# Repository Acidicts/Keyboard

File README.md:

# Keyboard

Sooo, this is a keyboard with a fun little oled display (via i2c) and rotary encoder with some rgb leds, following a modified ansi layout: `"` and `@` are swapped

### Features
- Powered via usb-c
- Wired keyboard
- RP2354A (2MB on onboard memory)
- RGB LEDS

### Models
- [Keyboard Assembly  (web)](https://a360.co/476DL3y)
- [Keyboard Assembly  (f3z)](Assembly.f3z)
- [Keyboard Case      (step)](./case/Case.step)
- [Keyboard Top Plate (step)](./case/Top-Plate.step)

### Assembly
- The case is a bit bigger than most 3d printers so you may need a 3rd party service for it
- Any ansi keycap set compatible with 75% keyboards should work i have not included price for them as you can make them in many ways,  either buy, 3d print, etc
- feel free to swap the `@` and `"` back if you prefer it that way just edit the [main.py](/firmware/main.py)
1. I recommend using PCBA for the top layer as those parts may be difficult to solder
2. On arrival of your half made pcb, start with soldering on the diodes facing in the direction of the silkscreen diagram
3. After solder on the rgb leds matching the notch up to the silkscreen too
4. Finally solder on your key switches to the board (I didn't want to give anyone the pain of manually soldering hot swaps on)
5. Put on your keycaps to key switches
6. Use a soldering iron to put in a m3 heat insert into the hole in the case
7. Put the pcb in the case
8. use a m3 screw to firmly mount to case but be wary of the underneath components so use spacers for it

### Case
[case](/case/Case.step)
[https://a360.co/476DL3y](https://a360.co/476DL3y)

### Firmware
1. Download the latest release of circuitpython from [here](https://downloads.circuitpython.org/bin/seeeduino_xiao_rp2040/en_GB/adafruit-circuitpython-seeeduino_xiao_rp2040-en_GB-10.3.0.uf2)
2. whilst powering the board (by plugging in usbc) hold down the boot button(labelled as `SW1` and plug it into your computer. The board should show up as a USB drive called `RPI-RP2` or something similar.
3. Drag and drop the downloaded UF2 file onto the `RPI-RP2` drive. The board will reboot and show up as a USB drive called `CIRCUITPY`.
4. drag and drop the contents of the [`firmware`](./firmware) folder onto the `CIRCUITPY` drive.
5. Restart the board and it should now be ready to use.

### BOMs
| Name | Link |
| --- | --- |
| Overview | [here](./BOM.csv) |
| LCSC List (included in addition parts) | [here](./BOMS/LCSC_BOM.csv) |
| PCBA Parts | [here](./BOMS/jlcpcb_pcb_BOM.csv) |

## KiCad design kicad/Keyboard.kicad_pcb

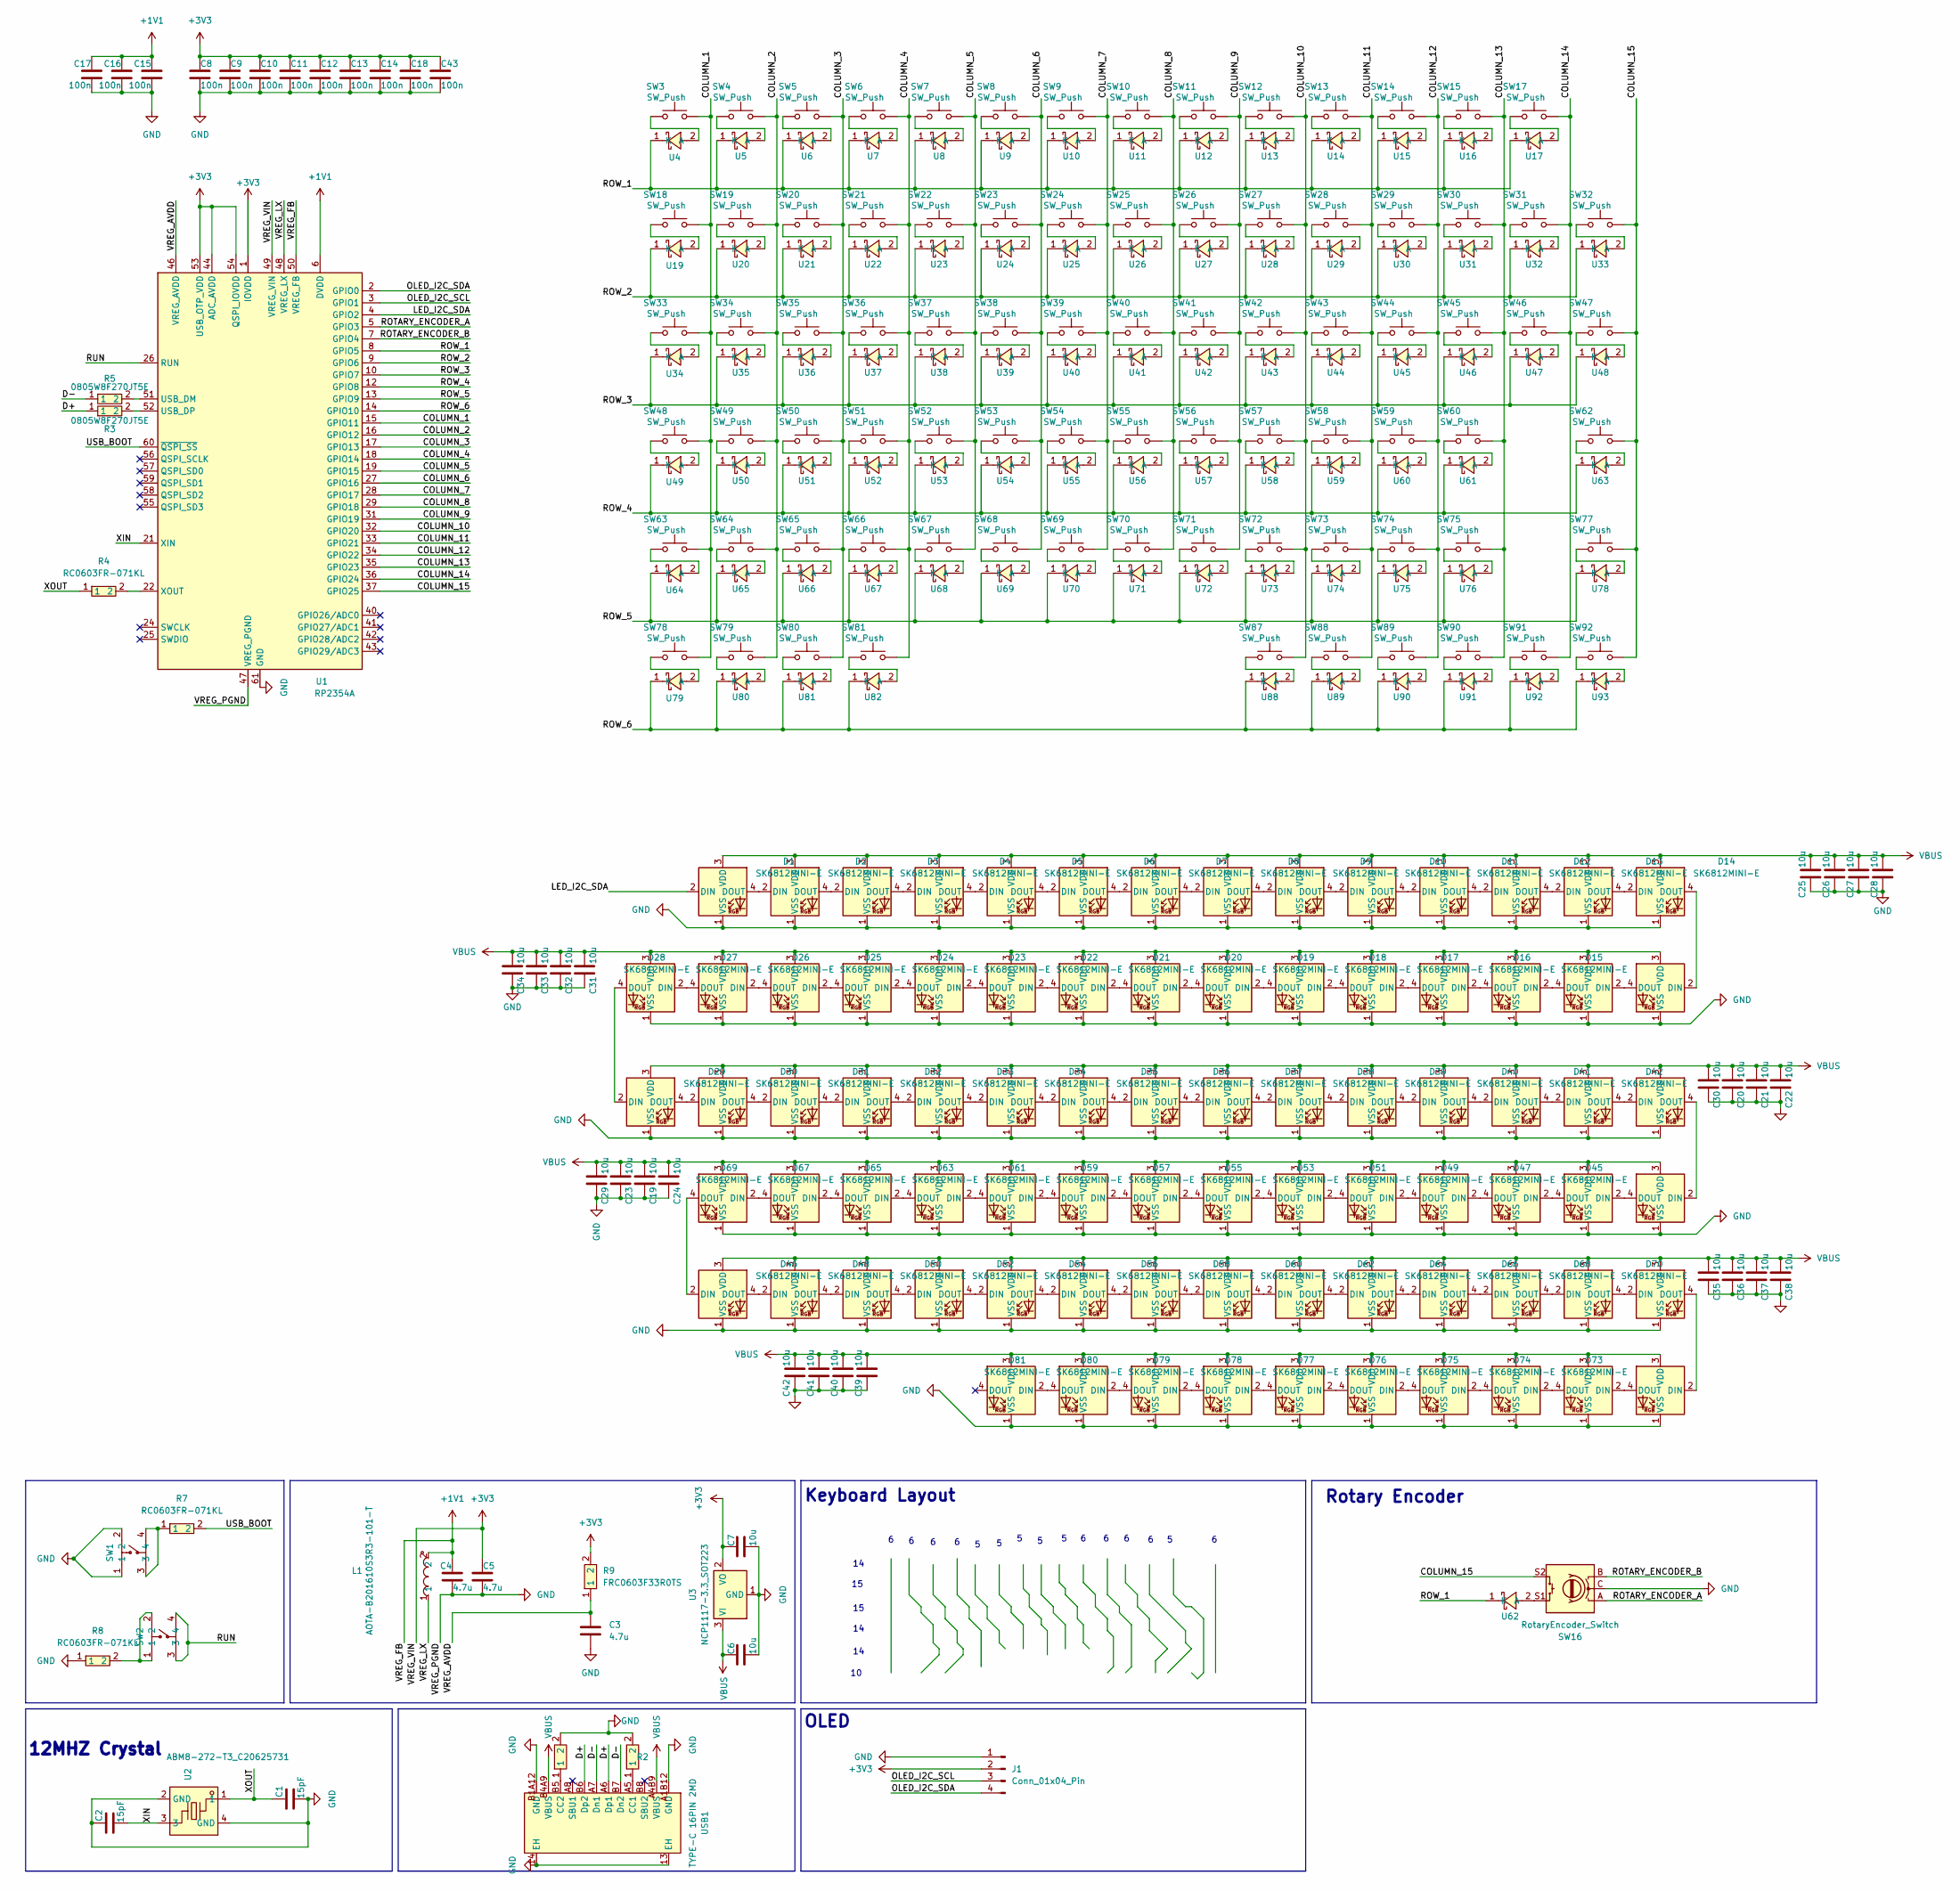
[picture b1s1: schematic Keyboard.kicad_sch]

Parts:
C1, C2: 15pF; C_0603_1608Metric
C3, C4, C5: 4.7u; C_0603_1608Metric
C6, C7, C19, C20, C21, C22, C23, C24, C25, C26, C27, C28, C29, C30, C31, C32, C33, C34, C35, C36, C37, C38, C39, C40, C41, C42: 10u; C_0805_2012Metric
C8, C9, C10, C11, C12, C13, C14, C15, C16, C17, C18, C43: 100n; C_0603_1608Metric
D1, D2, D3, D4, D5, D6, D7, D8, D9, D10, D11, D12, D13, D14, D15, D16, D17, D18, D19, D20, D21, D22, D23, D24, D25, D26, D27, D28, D29, D30, D31, D32, D33, D34, D35, D36, D37, D38, D39, D40, D41, D42, D43, D44, D45, D46, D47, D48, D49, D50, D51, D52, D53, D54, D55, D56, D57, D58, D59, D60, D61, D62, D63, D64, D65, D66, D67, D68, D69, D70, D71, D72, D73, D74, D75, D76, D77, D78, D79, D80, D81, D82: SK6812MINI-E; LED_SK6812MINI-E_3.2x2.8mm_P1.5mm_ReverseMount
J1: Conn_01x04_Pin; SSD1306_OLED_0.96
L1: AOTA-B201610S3R3-101-T; IND-SMD_L2.0-W1.6_AOTA-B201610S3R3-101-T; MPN AOTA-B201610S3R3-101-T; LCSC Part C42411119
R1, R2: FRC0603F5101TS; R0603; MPN FRC0603F5101TS; LCSC Part C2907044
R3, R5: 0805W8F270JT5E; R0805; MPN 0805W8F270JT5E; LCSC Part C17594
R4, R7, R8: RC0603FR-071KL; R_0603_1608Metric; MPN RC0603FR-071KL; LCSC Part C22548
R9: FRC0603F33R0TS; R0603; MPN FRC0603F33R0TS; LCSC Part C2909394
SW1, SW2: HX 3X4X2.5-PA-4N PUSH BUTTON SWITCH; SW-SMD_4P-L4.2-W3.4-P2.15-LS5.2; MPN HX 3x4x2.5-PA-4N push button switch; LCSC Part C55200589
SW3, SW4, SW5, SW6, SW7, SW8, SW9, SW10, SW11, SW12, SW13, SW14, SW15, SW17, SW18, SW19, SW20, SW21, SW22, SW23, SW24, SW25, SW26, SW27, SW28, SW29, SW30, SW32, SW34, SW35, SW36, SW37, SW38, SW39, SW40, SW41, SW42, SW43, SW44, SW45, SW47, SW49, SW50, SW51, SW52, SW53, SW54, SW55, SW56, SW57, SW58, SW59, SW62, SW64, SW65, SW66, SW67, SW68, SW69, SW70, SW71, SW72, SW73, SW75, SW77, SW87, SW88, SW89, SW90, SW91, SW92: SW_Push; SW_Cherry_MX_1.00u_PCB
SW16: RotaryEncoder_Switch; RotaryEncoder_Alps_EC11E-Switch_Vertical_H20mm
SW31, SW48, SW60: SW_Push; SW_Cherry_MX_2.00u_PCB
SW33, SW46: SW_Push; SW_Cherry_MX_1.50u_PCB
SW63: SW_Push; SW_Cherry_MX_2.25u_PCB
SW74: SW_Push; SW_Cherry_MX_1.75u_PCB
SW78: SW_Push; SW_Cherry_MX_1.25u_PCB
SW79, SW80: SW_Push; SW_Cherry_MX_1.25u_Plate
SW81: SW_Push; SW_Cherry_MX_6.25u_PCB
U1: RP2354A; QFN-60-1EP_7x7mm_P0.4mm_EP3.4x3.4mm
U2: ABM8-272-T3_C20625731; CRYSTAL-SMD_4P-L3.2-W2.5-BL; MPN ABM8-272-T3; LCSC Part C20625731
U3: NCP1117-3.3_SOT223; SOT-223-3_TabPin2
U4, U5, U6, U7, U8, U9, U10, U11, U12, U13, U14, U15, U16, U17, U19, U20, U21, U22, U23, U24, U25, U26, U27, U28, U29, U30, U31, U32, U33, U34, U35, U36, U37, U38, U39, U40, U41, U42, U43, U44, U45, U46, U47, U48, U49, U50, U51, U52, U53, U54, U55, U56, U57, U58, U59, U60, U61, U62, U63, U64, U65, U66, U67, U68, U69, U70, U71, U72, U73, U74, U75, U76, U78, U79, U80, U81, U82, U88, U89, U90, U91, U92, U93: MBR0530_C5204746; SOD-123_L2.7-W1.6-LS3.7-RD-1; MPN MBR0530; LCSC Part C5204746
USB1: TYPE-C 16PIN 2MD; USB-C-SMD_TYPE-C-16PIN-2MD-073; MPN TYPE-C 16PIN 2MD(073); LCSC Part C2765186

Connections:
+1V1: C4.1, C15.1, C16.1, C17.1, L1.2, U1.6 (DVDD), U1.23 (DVDD), U1.39 (DVDD), U1.50 (VREG_FB)
+3V3: C5.1, C7.1, C8.1, C9.1, C10.1, C11.1, C12.1, C13.1, C14.1, C18.1, C43.1, J1.2, R9.2, U1.1 (IOVDD), U1.11 (IOVDD), U1.20 (IOVDD), U1.30 (IOVDD), U1.38 (IOVDD), U1.44 (ADC_AVDD), U1.45 (IOVDD), U1.49 (VREG_VIN), U1.53 (USB_OTP_VDD), U1.54 (QSPI_IOVDD), U3.2 (VO)
/COLUMN_1: SW3.2, SW18.2, SW33.2, SW48.2, SW63.2, SW78.2, U1.15 (GPIO11)
/COLUMN_2: SW4.2, SW19.2, SW34.2, SW49.2, SW64.2, SW79.2, U1.16 (GPIO12)
/COLUMN_3: SW5.2, SW20.2, SW35.2, SW50.2, SW65.2, SW80.2, U1.17 (GPIO13)
/COLUMN_4: SW6.2, SW21.2, SW36.2, SW51.2, SW66.2, SW81.2, U1.18 (GPIO14)
/COLUMN_5: SW7.2, SW22.2, SW37.2, SW52.2, SW67.2, U1.19 (GPIO15)
/COLUMN_6: SW8.2, SW23.2, SW38.2, SW53.2, SW68.2, U1.27 (GPIO16)
/COLUMN_7: SW9.2, SW24.2, SW39.2, SW54.2, SW69.2, U1.28 (GPIO17)
/COLUMN_8: SW10.2, SW25.2, SW40.2, SW55.2, SW70.2, U1.29 (GPIO18)
/COLUMN_9: SW11.2, SW26.2, SW41.2, SW56.2, SW71.2, U1.31 (GPIO19)
/COLUMN_10: SW12.2, SW27.2, SW42.2, SW57.2, SW72.2, SW87.2, U1.32 (GPIO20)
/COLUMN_11: SW13.2, SW28.2, SW43.2, SW58.2, SW73.2, SW88.2, U1.33 (GPIO21)
/COLUMN_12: SW14.2, SW29.2, SW44.2, SW59.2, SW74.2, SW89.2, U1.34 (GPIO22)
/COLUMN_13: SW15.2, SW30.2, SW45.2, SW60.2, SW75.2, SW90.2, U1.35 (GPIO23)
/COLUMN_14: SW17.2, SW31.2, SW46.2, SW91.2, U1.36 (GPIO24)
/COLUMN_15: SW16.S2, SW32.2, SW47.2, SW62.2, SW77.2, SW92.2, U1.37 (GPIO25)
/D+: R3.1, USB1.A6 (Dp1), USB1.B6 (Dp2)
/D-: R5.1, USB1.A7 (Dn1), USB1.B7 (Dn2)
/LED_I2C_SDA: D1.2 (DIN), U1.4 (GPIO2)
/OLED_I2C_SCL: J1.3, U1.3 (GPIO1)
/OLED_I2C_SDA: J1.4, U1.2 (GPIO0)
/ROTARY_ENCODER_A: SW16.A, U1.5 (GPIO3)
/ROTARY_ENCODER_B: SW16.B, U1.7 (GPIO4)
/ROW_1: U1.8 (GPIO5), U4.1 (K), U5.1 (K), U6.1 (K), U7.1 (K), U8.1 (K), U9.1 (K), U10.1 (K), U11.1 (K), U12.1 (K), U13.1 (K), U14.1 (K), U15.1 (K), U16.1 (K), U17.1 (K), U62.1 (K)
/ROW_2: U1.9 (GPIO6), U19.1 (K), U20.1 (K), U21.1 (K), U22.1 (K), U23.1 (K), U24.1 (K), U25.1 (K), U26.1 (K), U27.1 (K), U28.1 (K), U29.1 (K), U30.1 (K), U31.1 (K), U32.1 (K), U33.1 (K)
/ROW_3: U1.10 (GPIO7), U34.1 (K), U35.1 (K), U36.1 (K), U37.1 (K), U38.1 (K), U39.1 (K), U40.1 (K), U41.1 (K), U42.1 (K), U43.1 (K), U44.1 (K), U45.1 (K), U46.1 (K), U47.1 (K), U48.1 (K)
/ROW_4: U1.12 (GPIO8), U49.1 (K), U50.1 (K), U51.1 (K), U52.1 (K), U53.1 (K), U54.1 (K), U55.1 (K), U56.1 (K), U57.1 (K), U58.1 (K), U59.1 (K), U60.1 (K), U61.1 (K), U63.1 (K)
/ROW_5: U1.13 (GPIO9), U64.1 (K), U65.1 (K), U66.1 (K), U67.1 (K), U68.1 (K), U69.1 (K), U70.1 (K), U71.1 (K), U72.1 (K), U73.1 (K), U74.1 (K), U75.1 (K), U76.1 (K), U78.1 (K)
/ROW_6: U1.14 (GPIO10), U79.1 (K), U80.1 (K), U81.1 (K), U82.1 (K), U88.1 (K), U89.1 (K), U90.1 (K), U91.1 (K), U92.1 (K), U93.1 (K)
/RUN: SW2.3, SW2.4, U1.26 (RUN)
/USB_BOOT: R7.2, U1.60 (~QSPI_SS)
/VREG_AVDD: C3.1, R9.1, U1.46 (VREG_AVDD)
/VREG_LX: L1.1, U1.48 (VREG_LX)
/XIN: C2.2, U1.21 (XIN), U2.3
/XOUT: C1.1, R4.1, U2.1
GND: C1.2, C2.1, C3.2, C4.2, C5.2, C6.2, C7.2, C8.2, C9.2, C10.2, C11.2, C12.2, C13.2, C14.2, C15.2, C16.2, C17.2, C18.2, C19.1, C20.1, C21.1, C22.1, C23.1, C24.1, C25.1, C26.1, C27.1, C28.1, C29.1, C30.1, C31.1, C32.1, C33.1, C34.1, C35.1, C36.1, C37.1, C38.1, C39.1, C40.1, C41.1, C42.1, C43.2, D1.1 (VSS), D2.1 (VSS), D3.1 (VSS), D4.1 (VSS), D5.1 (VSS), D6.1 (VSS), D7.1 (VSS), D8.1 (VSS), D9.1 (VSS), D10.1 (VSS), D11.1 (VSS), D12.1 (VSS), D13.1 (VSS), D14.1 (VSS), D15.1 (VSS), D16.1 (VSS), D17.1 (VSS), D18.1 (VSS), D19.1 (VSS), D20.1 (VSS), D21.1 (VSS), D22.1 (VSS), D23.1 (VSS), D24.1 (VSS), D25.1 (VSS), D26.1 (VSS), D27.1 (VSS), D28.1 (VSS), D29.1 (VSS), D30.1 (VSS), D31.1 (VSS), D32.1 (VSS), D33.1 (VSS), D34.1 (VSS), D35.1 (VSS), D36.1 (VSS), D37.1 (VSS), D38.1 (VSS), D39.1 (VSS), D40.1 (VSS), D41.1 (VSS), D42.1 (VSS), D43.1 (VSS), D44.1 (VSS), D45.1 (VSS), D46.1 (VSS), D47.1 (VSS), D48.1 (VSS), D49.1 (VSS), D50.1 (VSS), D51.1 (VSS), D52.1 (VSS), D53.1 (VSS), D54.1 (VSS), D55.1 (VSS), D56.1 (VSS), D57.1 (VSS), D58.1 (VSS), D59.1 (VSS), D60.1 (VSS), D61.1 (VSS), D62.1 (VSS), D63.1 (VSS), D64.1 (VSS), D65.1 (VSS), D66.1 (VSS), D67.1 (VSS), D68.1 (VSS), D69.1 (VSS), D70.1 (VSS), D71.1 (VSS), D72.1 (VSS), D73.1 (VSS), D74.1 (VSS), D75.1 (VSS), D76.1 (VSS), D77.1 (VSS), D78.1 (VSS), D79.1 (VSS), D80.1 (VSS), D81.1 (VSS), D82.1 (VSS), J1.1, R1.2, R2.2, R8.1, SW1.1, SW1.2, SW16.C, U1.47 (VREG_PGND), U1.61 (GND), U2.2 (GND), U2.4 (GND), U3.1 (GND), USB1.13 (EH), USB1.14 (EH), USB1.A1B12 (GND), USB1.B1A12 (GND)
unnamed: D1.4 (DOUT), D2.2 (DIN)
unnamed: D2.4 (DOUT), D3.2 (DIN)
unnamed: D3.4 (DOUT), D4.2 (DIN)
unnamed: D4.4 (DOUT), D5.2 (DIN)
unnamed: D5.4 (DOUT), D6.2 (DIN)
unnamed: D6.4 (DOUT), D7.2 (DIN)
unnamed: D7.4 (DOUT), D8.2 (DIN)
unnamed: D8.4 (DOUT), D9.2 (DIN)
unnamed: D9.4 (DOUT), D10.2 (DIN)
unnamed: D10.4 (DOUT), D11.2 (DIN)
unnamed: D11.4 (DOUT), D12.2 (DIN)
unnamed: D12.4 (DOUT), D13.2 (DIN)
unnamed: D13.4 (DOUT), D14.2 (DIN)
unnamed: D14.4 (DOUT), D15.2 (DIN)
unnamed: D15.4 (DOUT), D16.2 (DIN)
unnamed: D16.4 (DOUT), D17.2 (DIN)
unnamed: D17.4 (DOUT), D18.2 (DIN)
unnamed: D18.4 (DOUT), D19.2 (DIN)
unnamed: D19.4 (DOUT), D20.2 (DIN)
unnamed: D20.4 (DOUT), D21.2 (DIN)
unnamed: D21.4 (DOUT), D22.2 (DIN)
unnamed: D22.4 (DOUT), D23.2 (DIN)
unnamed: D23.4 (DOUT), D24.2 (DIN)
unnamed: D24.4 (DOUT), D25.2 (DIN)
unnamed: D25.4 (DOUT), D26.2 (DIN)
unnamed: D26.4 (DOUT), D27.2 (DIN)
unnamed: D27.4 (DOUT), D28.2 (DIN)
unnamed: D28.4 (DOUT), D43.2 (DIN)
unnamed: D29.2 (DIN), D43.4 (DOUT)
unnamed: D29.4 (DOUT), D30.2 (DIN)
unnamed: D30.4 (DOUT), D31.2 (DIN)
unnamed: D31.4 (DOUT), D32.2 (DIN)
unnamed: D32.4 (DOUT), D33.2 (DIN)
unnamed: D33.4 (DOUT), D34.2 (DIN)
unnamed: D34.4 (DOUT), D35.2 (DIN)
unnamed: D35.4 (DOUT), D36.2 (DIN)
unnamed: D36.4 (DOUT), D37.2 (DIN)
unnamed: D37.4 (DOUT), D38.2 (DIN)
unnamed: D38.4 (DOUT), D39.2 (DIN)
unnamed: D39.4 (DOUT), D40.2 (DIN)
unnamed: D40.4 (DOUT), D41.2 (DIN)
unnamed: D41.4 (DOUT), D42.2 (DIN)
unnamed: D42.4 (DOUT), D44.2 (DIN)
unnamed: D44.4 (DOUT), D45.2 (DIN)
unnamed: D45.4 (DOUT), D47.2 (DIN)
unnamed: D46.2 (DIN), D71.4 (DOUT)
unnamed: D46.4 (DOUT), D48.2 (DIN)
unnamed: D47.4 (DOUT), D49.2 (DIN)
unnamed: D48.4 (DOUT), D50.2 (DIN)
unnamed: D49.4 (DOUT), D51.2 (DIN)
unnamed: D50.4 (DOUT), D52.2 (DIN)
unnamed: D51.4 (DOUT), D53.2 (DIN)
unnamed: D52.4 (DOUT), D54.2 (DIN)
unnamed: D53.4 (DOUT), D55.2 (DIN)
unnamed: D54.4 (DOUT), D56.2 (DIN)
unnamed: D55.4 (DOUT), D57.2 (DIN)
unnamed: D56.4 (DOUT), D58.2 (DIN)
unnamed: D57.4 (DOUT), D59.2 (DIN)
unnamed: D58.4 (DOUT), D60.2 (DIN)
unnamed: D59.4 (DOUT), D61.2 (DIN)
unnamed: D60.4 (DOUT), D62.2 (DIN)
unnamed: D61.4 (DOUT), D63.2 (DIN)
unnamed: D62.4 (DOUT), D64.2 (DIN)
unnamed: D63.4 (DOUT), D65.2 (DIN)
unnamed: D64.4 (DOUT), D66.2 (DIN)
unnamed: D65.4 (DOUT), D67.2 (DIN)
unnamed: D66.4 (DOUT), D68.2 (DIN)
unnamed: D67.4 (DOUT), D69.2 (DIN)
unnamed: D68.4 (DOUT), D70.2 (DIN)
unnamed: D69.4 (DOUT), D71.2 (DIN)
unnamed: D70.4 (DOUT), D72.2 (DIN)
unnamed: D72.4 (DOUT), D73.2 (DIN)
unnamed: D73.4 (DOUT), D74.2 (DIN)
unnamed: D74.4 (DOUT), D75.2 (DIN)
unnamed: D75.4 (DOUT), D76.2 (DIN)
unnamed: D76.4 (DOUT), D77.2 (DIN)
unnamed: D77.4 (DOUT), D78.2 (DIN)
unnamed: D78.4 (DOUT), D79.2 (DIN)
unnamed: D79.4 (DOUT), D80.2 (DIN)
unnamed: D80.4 (DOUT), D81.2 (DIN)
unnamed: D81.4 (DOUT), D82.2 (DIN)
unnamed: R7.1, SW1.3, SW1.4
unnamed: R8.2, SW2.1, SW2.2
unnamed: R5.2, U1.51 (USB_DM)
unnamed: R3.2, U1.52 (USB_DP)
unnamed: R4.2, U1.22 (XOUT)
unnamed: SW3.1, U4.2 (A)
unnamed: SW4.1, U5.2 (A)
unnamed: SW5.1, U6.2 (A)
unnamed: SW6.1, U7.2 (A)
unnamed: SW7.1, U8.2 (A)
unnamed: SW8.1, U9.2 (A)
unnamed: SW9.1, U10.2 (A)
unnamed: SW10.1, U11.2 (A)
unnamed: SW11.1, U12.2 (A)
unnamed: SW12.1, U13.2 (A)
unnamed: SW13.1, U14.2 (A)
unnamed: SW14.1, U15.2 (A)
unnamed: SW15.1, U16.2 (A)
unnamed: SW17.1, U17.2 (A)
unnamed: SW18.1, U19.2 (A)
unnamed: SW19.1, U20.2 (A)
unnamed: SW20.1, U21.2 (A)
unnamed: SW21.1, U22.2 (A)
unnamed: SW22.1, U23.2 (A)
unnamed: SW23.1, U24.2 (A)
unnamed: SW24.1, U25.2 (A)
unnamed: SW25.1, U26.2 (A)
unnamed: SW26.1, U27.2 (A)
unnamed: SW27.1, U28.2 (A)
unnamed: SW28.1, U29.2 (A)
unnamed: SW29.1, U30.2 (A)
unnamed: SW30.1, U31.2 (A)
unnamed: SW31.1, U32.2 (A)
unnamed: SW32.1, U33.2 (A)
unnamed: SW33.1, U34.2 (A)
unnamed: SW34.1, U35.2 (A)
unnamed: SW35.1, U36.2 (A)
unnamed: SW36.1, U37.2 (A)
unnamed: SW37.1, U38.2 (A)
unnamed: SW38.1, U39.2 (A)
unnamed: SW39.1, U40.2 (A)
unnamed: SW40.1, U41.2 (A)
unnamed: SW41.1, U42.2 (A)
unnamed: SW42.1, U43.2 (A)
unnamed: SW43.1, U44.2 (A)
unnamed: SW44.1, U45.2 (A)
unnamed: SW45.1, U46.2 (A)
unnamed: SW46.1, U47.2 (A)
unnamed: SW47.1, U48.2 (A)
unnamed: SW48.1, U49.2 (A)
unnamed: SW49.1, U50.2 (A)
unnamed: SW50.1, U51.2 (A)
unnamed: SW51.1, U52.2 (A)
unnamed: SW52.1, U53.2 (A)
unnamed: SW53.1, U54.2 (A)
unnamed: SW54.1, U55.2 (A)
unnamed: SW55.1, U56.2 (A)
unnamed: SW56.1, U57.2 (A)
unnamed: SW57.1, U58.2 (A)
unnamed: SW58.1, U59.2 (A)
unnamed: SW59.1, U60.2 (A)
unnamed: SW60.1, U61.2 (A)
unnamed: SW16.S1, U62.2 (A)
unnamed: SW62.1, U63.2 (A)
unnamed: SW63.1, U64.2 (A)
unnamed: SW64.1, U65.2 (A)
unnamed: SW65.1, U66.2 (A)
unnamed: SW66.1, U67.2 (A)
unnamed: SW67.1, U68.2 (A)
unnamed: SW68.1, U69.2 (A)
unnamed: SW69.1, U70.2 (A)
unnamed: SW70.1, U71.2 (A)
unnamed: SW71.1, U72.2 (A)
unnamed: SW72.1, U73.2 (A)
unnamed: SW73.1, U74.2 (A)
unnamed: SW74.1, U75.2 (A)
unnamed: SW75.1, U76.2 (A)
unnamed: SW77.1, U78.2 (A)
unnamed: SW78.1, U79.2 (A)
unnamed: SW79.1, U80.2 (A)
unnamed: SW80.1, U81.2 (A)
unnamed: SW81.1, U82.2 (A)
unnamed: SW87.1, U88.2 (A)
unnamed: SW88.1, U89.2 (A)
unnamed: SW89.1, U90.2 (A)
unnamed: SW90.1, U91.2 (A)
unnamed: SW91.1, U92.2 (A)
unnamed: SW92.1, U93.2 (A)
unnamed: R2.1, USB1.A5 (CC1)
unnamed: R1.1, USB1.B5 (CC2)
VBUS: C6.1, C19.2, C20.2, C21.2, C22.2, C23.2, C24.2, C25.2, C26.2, C27.2, C28.2, C29.2, C30.2, C31.2, C32.2, C33.2, C34.2, C35.2, C36.2, C37.2, C38.2, C39.2, C40.2, C41.2, C42.2, D1.3 (VDD), D2.3 (VDD), D3.3 (VDD), D4.3 (VDD), D5.3 (VDD), D6.3 (VDD), D7.3 (VDD), D8.3 (VDD), D9.3 (VDD), D10.3 (VDD), D11.3 (VDD), D12.3 (VDD), D13.3 (VDD), D14.3 (VDD), D15.3 (VDD), D16.3 (VDD), D17.3 (VDD), D18.3 (VDD), D19.3 (VDD), D20.3 (VDD), D21.3 (VDD), D22.3 (VDD), D23.3 (VDD), D24.3 (VDD), D25.3 (VDD), D26.3 (VDD), D27.3 (VDD), D28.3 (VDD), D29.3 (VDD), D30.3 (VDD), D31.3 (VDD), D32.3 (VDD), D33.3 (VDD), D34.3 (VDD), D35.3 (VDD), D36.3 (VDD), D37.3 (VDD), D38.3 (VDD), D39.3 (VDD), D40.3 (VDD), D41.3 (VDD), D42.3 (VDD), D43.3 (VDD), D44.3 (VDD), D45.3 (VDD), D46.3 (VDD), D47.3 (VDD), D48.3 (VDD), D49.3 (VDD), D50.3 (VDD), D51.3 (VDD), D52.3 (VDD), D53.3 (VDD), D54.3 (VDD), D55.3 (VDD), D56.3 (VDD), D57.3 (VDD), D58.3 (VDD), D59.3 (VDD), D60.3 (VDD), D61.3 (VDD), D62.3 (VDD), D63.3 (VDD), D64.3 (VDD), D65.3 (VDD), D66.3 (VDD), D67.3 (VDD), D68.3 (VDD), D69.3 (VDD), D70.3 (VDD), D71.3 (VDD), D72.3 (VDD), D73.3 (VDD), D74.3 (VDD), D75.3 (VDD), D76.3 (VDD), D77.3 (VDD), D78.3 (VDD), D79.3 (VDD), D80.3 (VDD), D81.3 (VDD), D82.3 (VDD), U3.3 (VI), USB1.A4B9 (VBUS), USB1.B4A9 (VBUS)

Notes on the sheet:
OLED
12MHZ Crystal
Keyboard Layout
Rotary Encoder

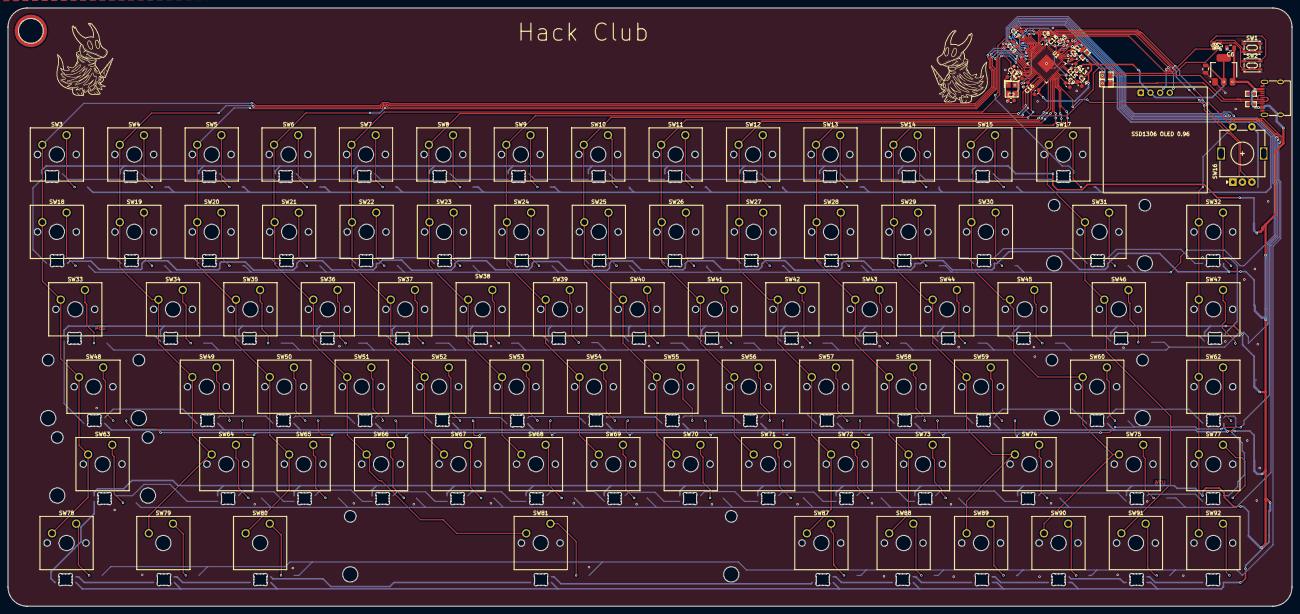
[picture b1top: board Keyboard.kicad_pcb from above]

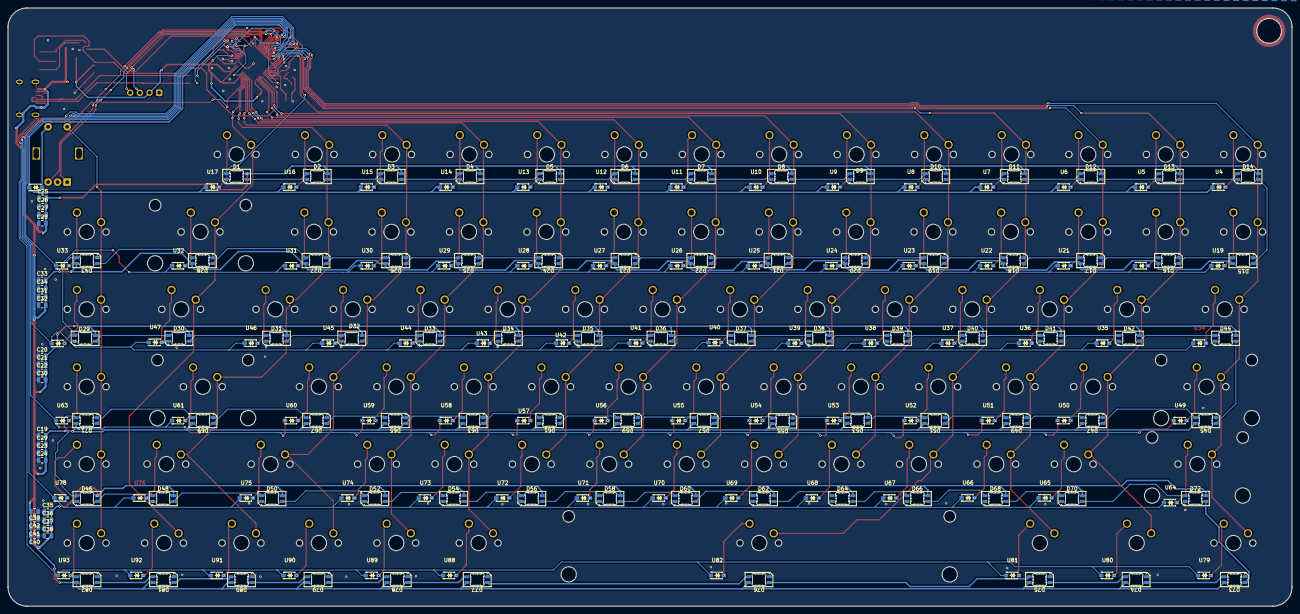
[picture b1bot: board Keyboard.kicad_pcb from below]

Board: 2 copper layers, 337.0 x 157.0 mm, 307 parts (189 on the bottom side), 209 nets.

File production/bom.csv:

Designator,Footprint,Quantity,Value,LCSC Part #
"C1, C2",0603,2,15pF,
"C10, C11, C12, C13, C14, C15, C16, C17, C18, C43, C8, C9",0603,12,100n,
"C19, C20, C21, C22, C23, C24, C25, C26, C27, C28, C29, C30, C31, C32, C33, C34, C35, C36, C37, C38, C39, C40, C41, C42, C6, C7",0805,26,10u,
"C3, C4, C5",0603,3,4.7u,
"D1, D10, D11, D12, D13, D14, D15, D16, D17, D18, D19, D2, D20, D21, D22, D23, D24, D25, D26, D27, D28, D29, D3, D30, D31, D32, D33, D34, D35, D36, D37, D38, D39, D4, D40, D41, D42, D43, D44, D45, D46, D47, D48, D49, D5, D50, D51, D52, D53, D54, D55, D56, D57, D58, D59, D6, D60, D61, D62, D63, D64, D65, D66, D67, D68, D69, D7, D70, D71, D72, D73, D74, D75, D76, D77, D78, D79, D8, D80, D81, D82, D9",LED_SK6812MINI-E_3.2x2.8mm_P1.5mm_ReverseMount,82,SK6812MINI-E,
J1,SSD1306_OLED_0.96,1,Conn_01x04_Pin,
L1,IND-SMD_L2.0-W1.6_AOTA-B201610S3R3-101-T,1,AOTA-B201610S3R3-101-T,C42411119
"R1, R2",R0603,2,FRC0603F5101TS,C2907044
"R3, R5",R0805,2,0805W8F270JT5E,C17594
"R4, R7, R8",0603,3,RC0603FR-071KL,C22548
R9,R0603,1,FRC0603F33R0TS,C2909394
"SW1, SW2",SW-SMD_4P-L4.2-W3.4-P2.15-LS5.2,2,HX 3X4X2.5-PA-4N PUSH BUTTON SWITCH,C55200589
"SW10, SW11, SW12, SW13, SW14, SW15, SW17, SW18, SW19, SW20, SW21, SW22, SW23, SW24, SW25, SW26, SW27, SW28, SW29, SW3, SW30, SW32, SW34, SW35, SW36, SW37, SW38, SW39, SW4, SW40, SW41, SW42, SW43, SW44, SW45, SW47, SW49, SW5, SW50, SW51, SW52, SW53, SW54, SW55, SW56, SW57, SW58, SW59, SW6, SW62, SW64, SW65, SW66, SW67, SW68, SW69, SW7, SW70, SW71, SW72, SW73, SW75, SW77, SW8, SW87, SW88, SW89, SW9, SW90, SW91, SW92",SW_Cherry_MX_1.00u_PCB,71,SW_Push,
SW16,RotaryEncoder_Alps_EC11E-Switch_Vertical_H20mm,1,RotaryEncoder_Switch,
"SW31, SW48, SW60",SW_Cherry_MX_2.00u_PCB,3,SW_Push,
"SW33, SW46",SW_Cherry_MX_1.50u_PCB,2,SW_Push,
SW63,SW_Cherry_MX_2.25u_PCB,1,SW_Push,
SW74,SW_Cherry_MX_1.75u_PCB,1,SW_Push,
SW78,SW_Cherry_MX_1.25u_PCB,1,SW_Push,
"SW79, SW80",SW_Cherry_MX_1.25u_Plate,2,SW_Push,
SW81,SW_Cherry_MX_6.25u_PCB,1,SW_Push,
U1,QFN-60-1EP_7x7mm_P0.4mm_EP3.4x3.4mm,1,RP2354A,
"U10, U11, U12, U13, U14, U15, U16, U17, U19, U20, U21, U22, U23, U24, U25, U26, U27, U28, U29, U30, U31, U32, U33, U34, U35, U36, U37, U38, U39, U4, U40, U41, U42, U43, U44, U45, U46, U47, U48, U49, U5, U50, U51, U52, U53, U54, U55, U56, U57, U58, U59, U6, U60, U61, U62, U63, U64, U65, U66, U67, U68, U69, U7, U70, U71, U72, U73, U74, U75, U76, U78, U79, U8, U80, U81, U82, U88, U89, U9, U90, U91, U92, U93",SOD-123_L2.7-W1.6-LS3.7-RD-1,83,MBR0530_C5204746,C5204746
U2,CRYSTAL-SMD_4P-L3.2-W2.5-BL,1,ABM8-272-T3_C20625731,C20625731
U3,SOT-223-3_TabPin2,1,NCP1117-3.3_SOT223,
USB1,USB-C-SMD_TYPE-C-16PIN-2MD-073,1,TYPE-C 16PIN 2MD,C2765186
